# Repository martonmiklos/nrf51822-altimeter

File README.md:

# nrf51822-altimeter
nRF51822 based altimeter board for model rockets

A small module built around a [WT51822-S4AT](https://www.tme.eu/hu/details/wt51822-s4at/iot-wifibluetooth-modulok/wireless-tag) BLE module.

Features a DPS310 barometer and an MMA8452Q accelerometer. 

Firmware code lives here:

https://github.com/martonmiklos/nrf51822-altimeter-fw

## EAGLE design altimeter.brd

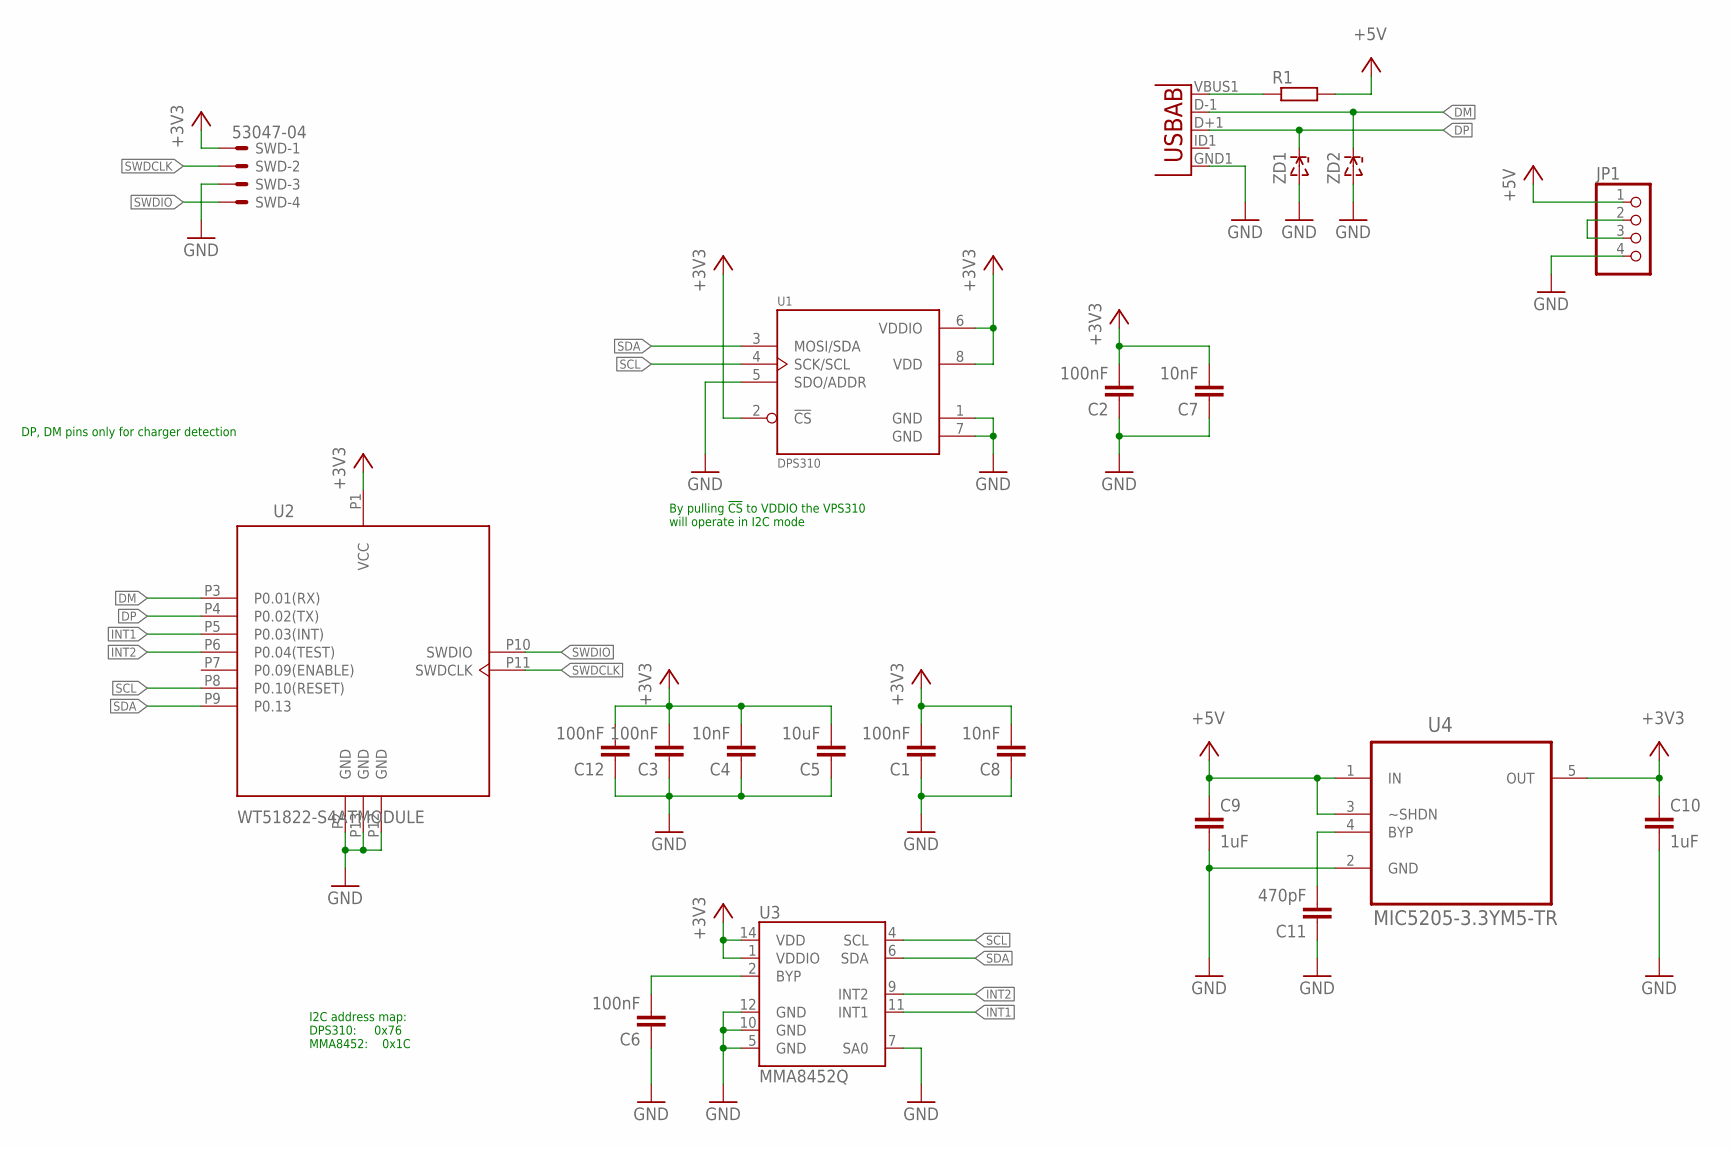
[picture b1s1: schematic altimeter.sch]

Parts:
C1, C2, C3, C6, C12: 100nF; C0603
C4, C7, C8: 10nF; C0603
C5: 10uF; C0805
C9, C10: 1uF; C0603
C11: 470pF; C0603
JP1: PINHD-1X4; 1X04
R1: R-EU_R0805; R0805
SWD: 53047-04
U1: DPS310; LGA8S145X65P2X4_200X250X100
U2: WT51822-S4ATMODULE; WT51822-S4AT
U3: MMA8452Q; QFN-16_0.5MM
U4: MIC5205-3.3YM5-TR; SOT95P280X145-5N
USB: USB-ABIN&OUT; USB-AB-MICRO-SMD-V03-IN&OUT
ZD1, ZD2: ZENERSOD-123; SOD-123

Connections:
+3V3: C1.2, C2.2, C3.2, C4.2, C5.2, C7.2, C8.2, C10.1, C12.2, SWD.1, U1.2 (!CS), U1.6 (VDDIO), U1.8 (VDD), U2.P1 (VCC), U3.1 (VDDIO), U3.14 (VDD), U4.5 (OUT)
+5V: C9.1, JP1.1, R1.2, U4.1 (IN), U4.3 (~SHDN)
DM: U2.P3 (P0.01(RX)), USB.D-1 (D-), ZD2.C
DP: U2.P4 (P0.02(TX)), USB.D+1 (D+), ZD1.C
GND: C1.1, C2.1, C3.1, C4.1, C5.1, C6.1, C7.1, C8.1, C9.2, C10.2, C11.1, C12.1, JP1.4, SWD.3, U1.1 (GND), U1.5 (SDO/ADDR), U1.7 (GND), U2.P2 (GND), U2.P12 (GND), U2.P13 (GND), U3.5 (GND), U3.7 (SA0), U3.10 (GND), U3.12 (GND), U4.2 (GND), USB.GND1 (GND), ZD1.A, ZD2.A
INT1: U2.P5 (P0.03(INT)), U3.11 (INT1)
INT2: U2.P6 (P0.04(TEST)), U3.9 (INT2)
unnamed: R1.1, USB.VBUS1 (VBUS)
unnamed: C6.2, U3.2 (BYP)
unnamed: JP1.2, JP1.3
unnamed: C11.2, U4.4 (BYP)
SCL: U1.4 (SCK/SCL), U2.P8 (P0.10(RESET)), U3.4 (SCL)
SDA: U1.3 (MOSI/SDA), U2.P9 (P0.13), U3.6 (SDA)
SWDCLK: SWD.2, U2.P11 (SWDCLK)
SWDIO: SWD.4, U2.P10 (SWDIO)

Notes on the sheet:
By pulling !CS! to VDDIO the VPS310 will operate in I2C mode
I2C address map: DPS310: 0x76 MMA8452: 0x1C
DP, DM pins only for charger detection

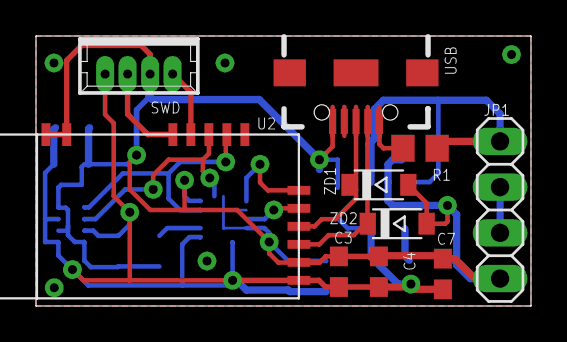
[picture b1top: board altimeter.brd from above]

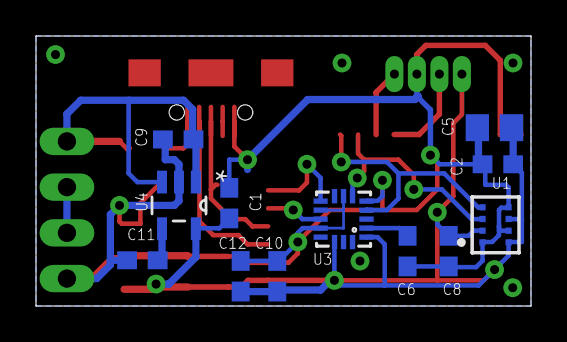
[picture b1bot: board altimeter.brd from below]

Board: 2 copper layers, 27.5 x 15.0 mm, 22 parts (12 on the bottom side), 15 nets.

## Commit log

2017-10-03 Initial add.
2017-10-12 Silkscreen cleanup before gerber export.
2018-05-19 Reorganized SCH

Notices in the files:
parts and their libraries:
SparkFun: Licensing: CC v3.0 Share-Alike You are welcome to use this library for commercial purposes.
